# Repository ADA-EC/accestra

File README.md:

# Accestra
 Sistema de entrada/saída de membros na sala da ADA.

<h2> Descrição </h2>

O objetivo é desenvolver e instalar um sistema de abertura da porta por meio dos cartões USP, a partir da comunicação em rádio frequência (RFID).
  
<h2> Tencologias Usadas </h2>

Para compor o sistema de acesso, foi utilizado um Arduino UNO, com planos de usarmos apenas o <b>ATmega</b>. A porta é equipada com um <b>leitor de RFID</b> e um <b>botão</b> interno, enquanto a tranca será substituída por uma <b>fechadura elétrica</b> comum, acionada por um sinal elétrico enviado pelo sistema. Haverá ainda um <b>buzzer</b> para alertas sonoros e um <b>LED vermelho e outro verde</b> para indicação do estado.<br><br>
Na programação foram utilizadas as bibliotecas <b>SPI</b> e <b>MFRC522</b>

<h2> Protótipo </h2>

<h2> Manual do Sistema </h2>

Um manual do sistema, contendo informações detalhadas sobre o código e sobre como operar estará disponível neste repostório 

<h2>Membros</h2>
<ul>
 <li>Érika Hortência</li>
 <li>Fernando Rosalini Calaza</li>
 <li>Marcos Pietrucci</li>
</ul>
<h2>Agradecimentos</h2>
<ul>
 <li>Alexandre Batistella Bellas</li>
 <li>Bruno Coulturato pelas contribuições no desenvolvimento da PCB</li>

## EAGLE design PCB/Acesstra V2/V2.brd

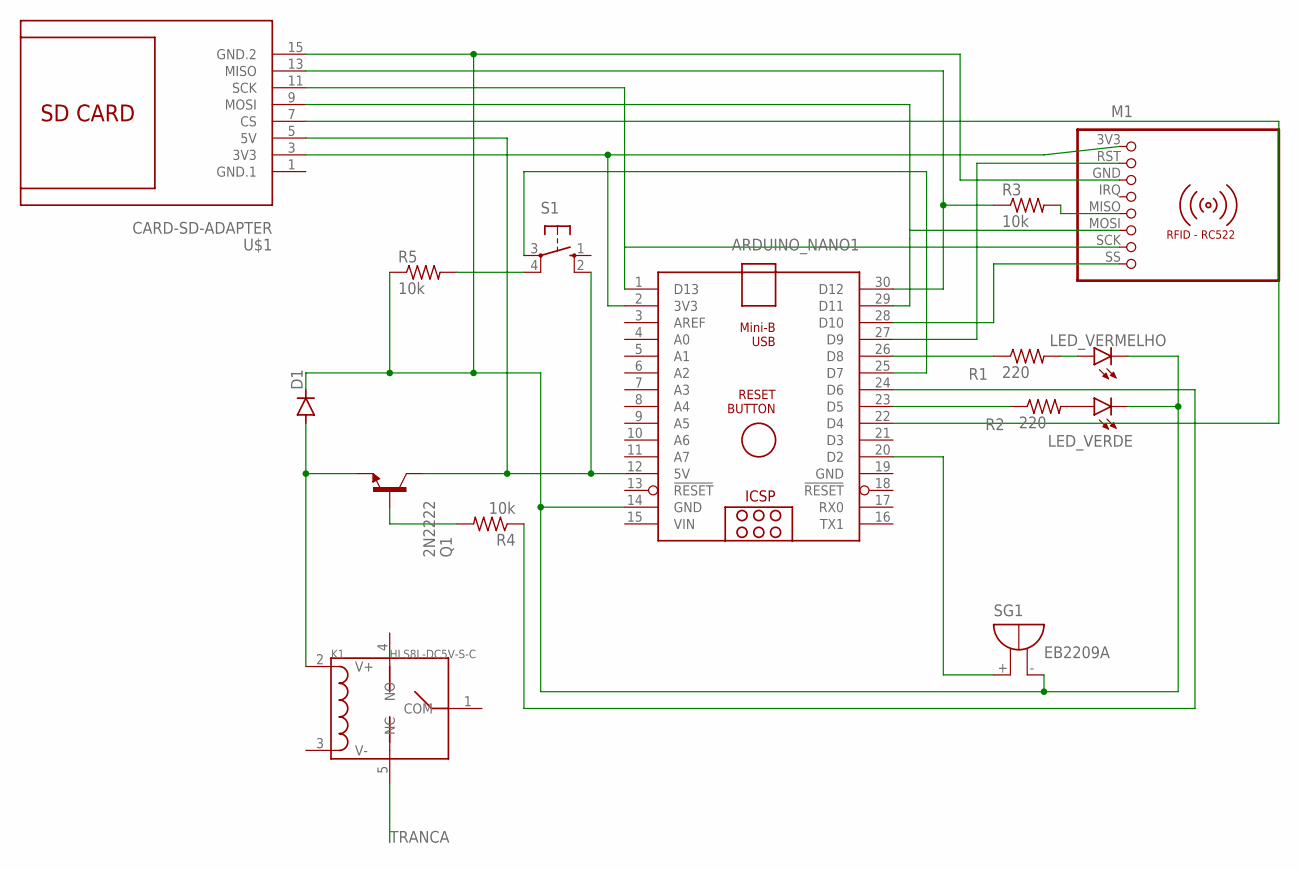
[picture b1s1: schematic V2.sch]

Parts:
ARDUINO_NANO1: ARDUINO_NANO
D1: 1N4148DO35-10; DO35-10
K1: HLS8L-DC5V-S-C; REY5-19.0X15.0X15.0MM
LED_VERDE: -LED; LED5
LED_VERMELHO: -LED; LED5
M1: RFID-RC522
Q1: 2N2222; TO92-CBE
R1, R2: 220; 0204/5
R3, R4, R5: 10k; 0204/5
S1: 10-XX; B3F-10XX
SG1: EB2209A
U$1: CARD-SD-ADAPTER

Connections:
GND: ARDUINO_NANO1.19 (GND)
GND.1: U$1.1 (GND.1)
unnamed: ARDUINO_NANO1.20 (D2), SG1.+
unnamed: LED_VERMELHO.ANODE, R1.2
unnamed: LED_VERDE.ANODE, R2.2
unnamed: ARDUINO_NANO1.26 (D8), R1.1
unnamed: ARDUINO_NANO1.23 (D5), R2.1
unnamed: ARDUINO_NANO1.24 (D6), R4.1
unnamed: D1.A, K1.2 (V+), Q1.E
unnamed: Q1.B, R4.2
unnamed: ARDUINO_NANO1.14 (GND), D1.C, LED_VERDE.CATHODE, LED_VERMELHO.CATHODE, M1.GND (3), R5.1, SG1.-, U$1.15 (GND.2)
unnamed: ARDUINO_NANO1.12 (5V), Q1.C, S1.2 (S1), U$1.5 (5V)
unnamed: ARDUINO_NANO1.25 (D7), S1.3
unnamed: ARDUINO_NANO1.2 (3V3), M1.3V3 (1), U$1.3 (3V3)
unnamed: R5.2, S1.4 (P1)
unnamed: ARDUINO_NANO1.27 (D9), M1.RST (2)
unnamed: M1.MISO (5), R3.2
unnamed: ARDUINO_NANO1.30 (D12), R3.1, U$1.13 (MISO)
unnamed: ARDUINO_NANO1.29 (D11), M1.MOSI (6), U$1.9 (MOSI)
unnamed: ARDUINO_NANO1.22 (D4), U$1.7 (CS)
unnamed: ARDUINO_NANO1.28 (D10), M1.SS (8)
unnamed: ARDUINO_NANO1.1 (D13), M1.SCK (7), U$1.11 (SCK)
TRANCA: K1.5 (NC)
VIN: ARDUINO_NANO1.15 (VIN)

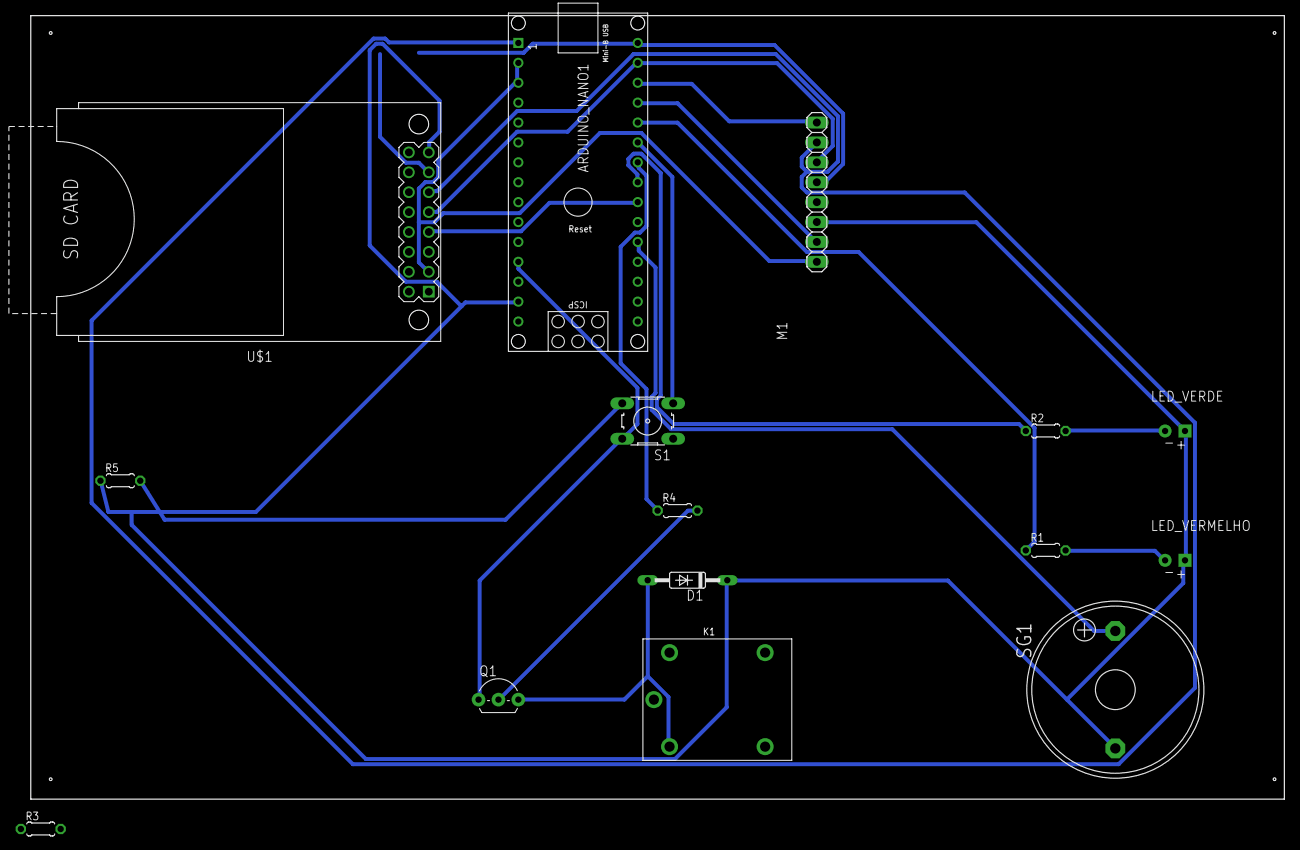
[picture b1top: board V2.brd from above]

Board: 2 copper layers, 160.0 x 100.0 mm, 15 parts (0 on the bottom side), 20 nets.

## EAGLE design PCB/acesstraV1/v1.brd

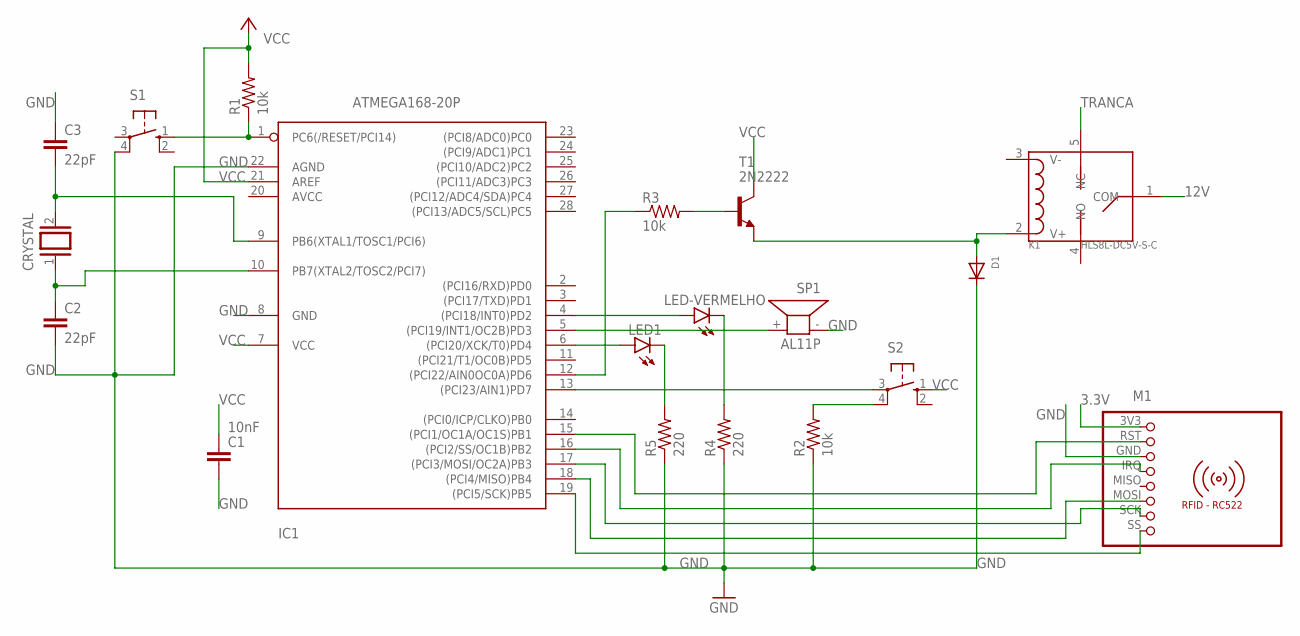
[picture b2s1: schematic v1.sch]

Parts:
C1: 10nF; C025-025X050
C2, C3: 22pF; C025-025X050
CRYSTAL: XTAL/S; QS
D1: DIODEDO-1N4148; DO-1N4148
IC1: ATMEGA168-20P; DIL28-3
K1: HLS8L-DC5V-S-C; REY5-19.0X15.0X15.0MM
LED1: LED5MM
LED-VERMELHO: LED5MM
M1: RFID-RC522
R1, R2, R3: 10k; 0204/7
R4, R5: 220; 0204/7
S1, S2: 10-XX; B3F-10XX
SP1: AL11P
T1: 2N2222; TO92-EBC-OVAL

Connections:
3.3V: M1.3V3 (1)
12V: K1.1 (COM)
GND: C1.2, C2.2, C3.1, D1.C, IC1.8 (GND), IC1.22 (AGND), M1.GND (3), R2.1, R4.1, R5.1, S1.4 (P1), SP1.- (1)
unnamed: IC1.1 (PC6(/RESET/PCI14)), R1.1, S1.1 (S)
unnamed: IC1.4 ((PCI18/INT0)PD2), LED-VERMELHO.A
unnamed: LED-VERMELHO.K (C), R4.2
unnamed: IC1.6 ((PCI20/XCK/T0)PD4), LED1.A
unnamed: LED1.K (C), R5.2
unnamed: IC1.5 ((PCI19/INT1/OC2B)PD3), SP1.+ (2)
unnamed: IC1.13 ((PCI23/AIN1)PD7), S2.3
unnamed: R2.2, S2.4 (P1)
unnamed: IC1.12 ((PCI22/AIN0OC0A)PD6), R3.1
unnamed: R3.2, T1.B
unnamed: D1.A, K1.2 (V+), T1.E
unnamed: C3.2, CRYSTAL.2, IC1.9 (PB6(XTAL1/TOSC1/PCI6))
unnamed: C2.1, CRYSTAL.1, IC1.10 (PB7(XTAL2/TOSC2/PCI7))
unnamed: IC1.15 ((PCI1/OC1A/OC1S)PB1), M1.RST (2)
unnamed: IC1.16 ((PCI2/SS/OC1B)PB2), M1.IRQ (4)
unnamed: IC1.17 ((PCI3/MOSI/OC2A)PB3), M1.SCK (7)
unnamed: IC1.18 ((PCI4/MISO)PB4), M1.MOSI (6)
unnamed: IC1.19 ((PCI5/SCK)PB5), M1.SS (8)
TRANCA: K1.5 (NC)
VCC: C1.1, IC1.7 (VCC), IC1.21 (AREF), R1.2, S2.1 (S), T1.C

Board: 2 copper layers, 19 parts (0 on the bottom side), 20 nets, no tracks yet.

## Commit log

2019-05-23 Commit teste
2019-11-09 Add files via upload
    O código é capaz de:
    -Indicar por meio de Leds se a porta está fechada ou aberta;
    -Abrir e fechar a porta, baseado na leitura de tags e cartões FRID dos membros. Se a tag ou cartão não pertencer a um membro, o acesso é negado (as interações são feitas via monitor Serial);
    -Por meio de botões auxiliares abrir e fechar a porta;
    -Registrar novos membros no sistema.
2019-11-12 Apenas um teste
2019-11-12 criar teste
2019-11-14 Adicionado a leitura do cartão SD, funcionando individualmente. A integração com o módulo RFID ainda é duvidosa
2019-11-14 Apenas retirei alguns resquicios de testes
2019-12-18 Mudanças iniciais - Retirada de tudo que lida com o armazenamento dos números permitidos e com dados dos membros
2019-12-18 Retoques: adição de comentários e remoção de comandos inúteis
2020-01-02 Update do Readme
    Atualização da lista dos membros
2020-01-04 Adicionando funcionalidades do buzzer
2020-01-06 Update - Melhorias no código
    - O pino 10 já estava em uso
    - Diminui a quantidade de bips ao fechar a porta
2020-01-06 Mudanças nos tons sonoros & Adição de som no modo de cadastro
2020-01-06 Melhorias e retoques no código
2020-03-16 Adição das exigências e início da descrição do nosso plano
2020-03-16 Adição da pauta da reunião com mais detalhes
2020-03-30 Pequenas alterações
2020-03-31 Ajustando o código para a trava elétrica
2020-04-02 Retirando acionamento dencessário
2020-04-23 Retirando o botão externo, que está inutilizado
2020-10-15 Adicionando primeiro esquematico - EAGLE
2020-10-15 Adicionando bibliotecas extras usadas
2021-01-03 Finalizado, após testes, a versão inicial do Accesstra
2021-01-07 Adicionando leitura de cartões USP! Além disso toda a lógica do programa foi alterada, aceitando TAGS, cartões USP ou qualquer outro dispositivo RFID compatível
2021-01-09 Descrições mais detalhadas do projeto
2021-01-09 Ajustando o repositório
2021-01-09 Adicionando imagem do protótipo
2021-01-09 Correções
2021-01-09 Adicionando imagem em PNG
2021-01-10 Ajustando imagem
2021-01-10 Ajustando imagem novamente
2021-01-10 Atualizando o README
2021-01-10 Ajustando README
2021-02-10 Versão inicial do Accesstra usando cartão SD
2021-02-23 Adicionando funcionalidades totais do cartão SD
2021-02-24 Refinando o uso do cartão SD
2021-03-02 Limpeza e ajuste do código
2021-03-02 Renomeando o arquivo
2021-03-02 Deletando arquivos
2021-03-05 Adição de comentários e pequenos ajustes após GC
2021-03-16 Adicionando alerta sonoro e visual de erro
2021-03-20 Ajustando a mensagem de erro do SD
2021-03-22 Upload da segunda versão da PCB
2021-03-22 Ajustes na PCB
2021-03-22 Ajuste da PCB
2021-04-09 Ajustes no aviso sonoro de erro. Agora é mais singular do que o aviso de cadastro/descadastro
2021-04-20 Removendo duplicação de aviso sonoro

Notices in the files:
parts and their libraries:
diy-modules: Released under the Creative Commons Attribution 4.0 International License: http://creativecommons.org/licenses/by/4.0
